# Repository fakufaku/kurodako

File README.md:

View this project on [CADLAB.io](https://cadlab.io/node/948). 

Kurodako
========

An eight-channel compact microphone array based on the Beaglebone Black and PDM microphones.

Bill of Materials
-----------------

* 8x SPM1437HM4H-B PDM MEMS Microphones (Mouser 721-SPM1437HM4H-B)
* 8x 100nF capacitors, 0805 package
* 2x pin headers 2x40, 2.54mm spaced

Possibly also:
* 4x 100 ohms resistors

If we want to use wires rather than only PCB microphones:
* 8x Micromatch Male-On-Wire 4 pin connector
* 8x Micromatch Female-One-Board 4 pin connector SMD
* flat cable, 1.27mm, 4 wires

Dependencies
------------

* The PRU code doing the low pass filtering [repo](https://github.com/Scrashdown/PRU-Audio-Processing) [Work in progress]

License
-------

2017 (c) Robin Scheibler

This board was designed by Robin Scheibler and is shared under the [Creative Commons CC-BY-SA](https://creativecommons.org/licenses/by-sa/4.0/) license.

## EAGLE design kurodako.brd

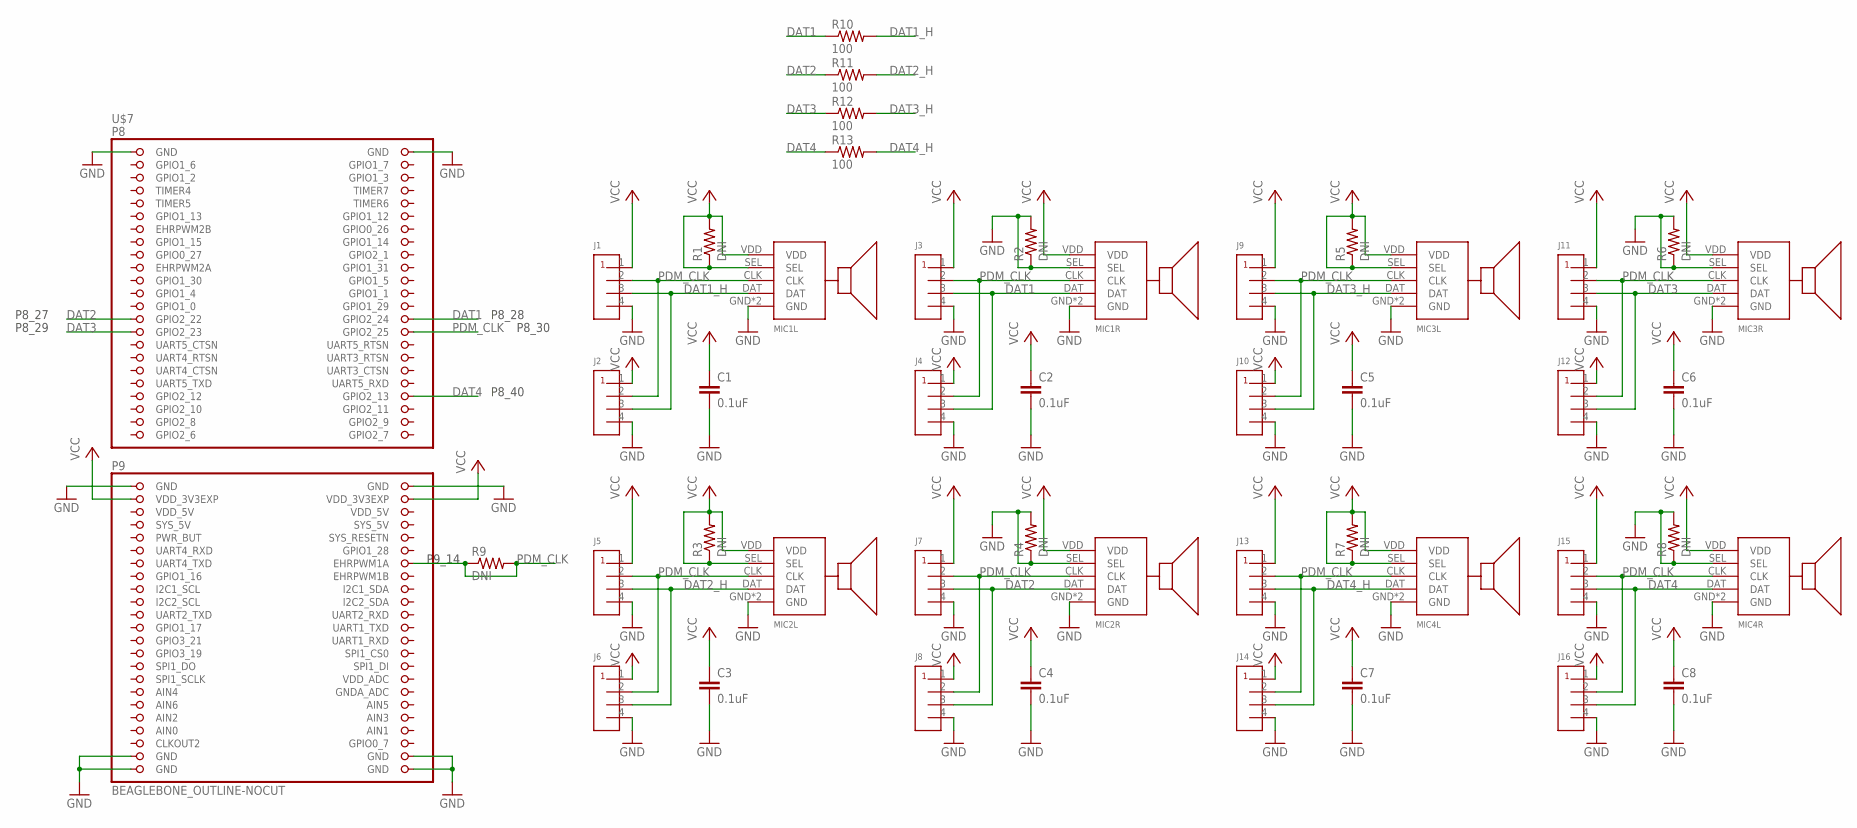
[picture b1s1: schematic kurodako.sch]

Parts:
C1, C2, C3, C4, C5, C6, C7, C8: 0.1uF; 0805
J1, J2, J3, J4, J5, J6, J7, J8, J9, J10, J11, J12, J13, J14, J15, J16: CONN-4P-MICROMATCH-SMD; MICROMATCH-4P-SMD
MIC1L, MIC1R, MIC2L, MIC2R, MIC3L, MIC3R, MIC4L, MIC4R: SPM1437HM4H-B; MEMS-MIC-6PAD
R1, R2, R3, R4, R5, R6, R7, R8, R9: DNI; R0805
R10, R11, R12, R13: 100; R0805
U$7: BEAGLEBONE_OUTLINE-NOCUT; BEAGLEBONE_SHIELD_NOCUT

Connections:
AIN0: U$7.85 (AIN0)
DAT1: J3.3, J4.3, MIC1R.DAT, R10.1, U$7.28 (GPIO2_24)
DAT1_H: J1.3, J2.3, MIC1L.DAT, R10.2
DAT2: J7.3, J8.3, MIC2R.DAT, R11.1, U$7.27 (GPIO2_22)
DAT2_H: J5.3, J6.3, MIC2L.DAT, R11.2
DAT3: J11.3, J12.3, MIC3R.DAT, R12.1, U$7.29 (GPIO2_23)
DAT3_H: J9.3, J10.3, MIC3L.DAT, R12.2
DAT4: J15.3, J16.3, MIC4R.DAT, R13.1, U$7.40 (GPIO2_13)
DAT4_H: J13.3, J14.3, MIC4L.DAT, R13.2
GND: C1.2, C2.2, C3.2, C4.2, C5.2, C6.2, C7.2, C8.2, J1.4, J2.4, J3.4, J4.4, J5.4, J6.4, J7.4, J8.4, J9.4, J10.4, J11.4, J12.4, J13.4, J14.4, J15.4, J16.4, MIC1L.GND, MIC1L.GND@1 (GND), MIC1R.GND, MIC1R.GND@1 (GND), MIC1R.SEL, MIC2L.GND, MIC2L.GND@1 (GND), MIC2R.GND, MIC2R.GND@1 (GND), MIC2R.SEL, MIC3L.GND, MIC3L.GND@1 (GND), MIC3R.GND, MIC3R.GND@1 (GND), MIC3R.SEL, MIC4L.GND, MIC4L.GND@1 (GND), MIC4R.GND, MIC4R.GND@1 (GND), MIC4R.SEL, R2.1, R2.2, R4.1, R4.2, R6.1, R6.2, R8.1, R8.2, U$7.1 (GND), U$7.2 (GND), U$7.47 (GND), U$7.48 (GND), U$7.89 (GND), U$7.90 (GND), U$7.91 (GND), U$7.92 (GND)
PDM_CLK: J1.2, J2.2, J3.2, J4.2, J5.2, J6.2, J7.2, J8.2, J9.2, J10.2, J11.2, J12.2, J13.2, J14.2, J15.2, J16.2, MIC1L.CLK, MIC1R.CLK, MIC2L.CLK, MIC2R.CLK, MIC3L.CLK, MIC3R.CLK, MIC4L.CLK, MIC4R.CLK, R9.1, R9.2, U$7.30 (GPIO2_25), U$7.60 (EHRPWM1A)
SYS_5V: U$7.53 (SYS_5V)
VCC: C1.1, C2.1, C3.1, C4.1, C5.1, C6.1, C7.1, C8.1, J1.1, J2.1, J3.1, J4.1, J5.1, J6.1, J7.1, J8.1, J9.1, J10.1, J11.1, J12.1, J13.1, J14.1, J15.1, J16.1, MIC1L.SEL, MIC1L.VDD, MIC1R.VDD, MIC2L.SEL, MIC2L.VDD, MIC2R.VDD, MIC3L.SEL, MIC3L.VDD, MIC3R.VDD, MIC4L.SEL, MIC4L.VDD, MIC4R.VDD, R1.1, R1.2, R3.1, R3.2, R5.1, R5.2, R7.1, R7.2, U$7.49 (VDD_3V3EXP), U$7.50 (VDD_3V3EXP)
VDD_5V: U$7.51 (VDD_5V), U$7.52 (VDD_5V)

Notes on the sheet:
P8_40
P8_27
P8_28
P8_29
P8_30
P9_14

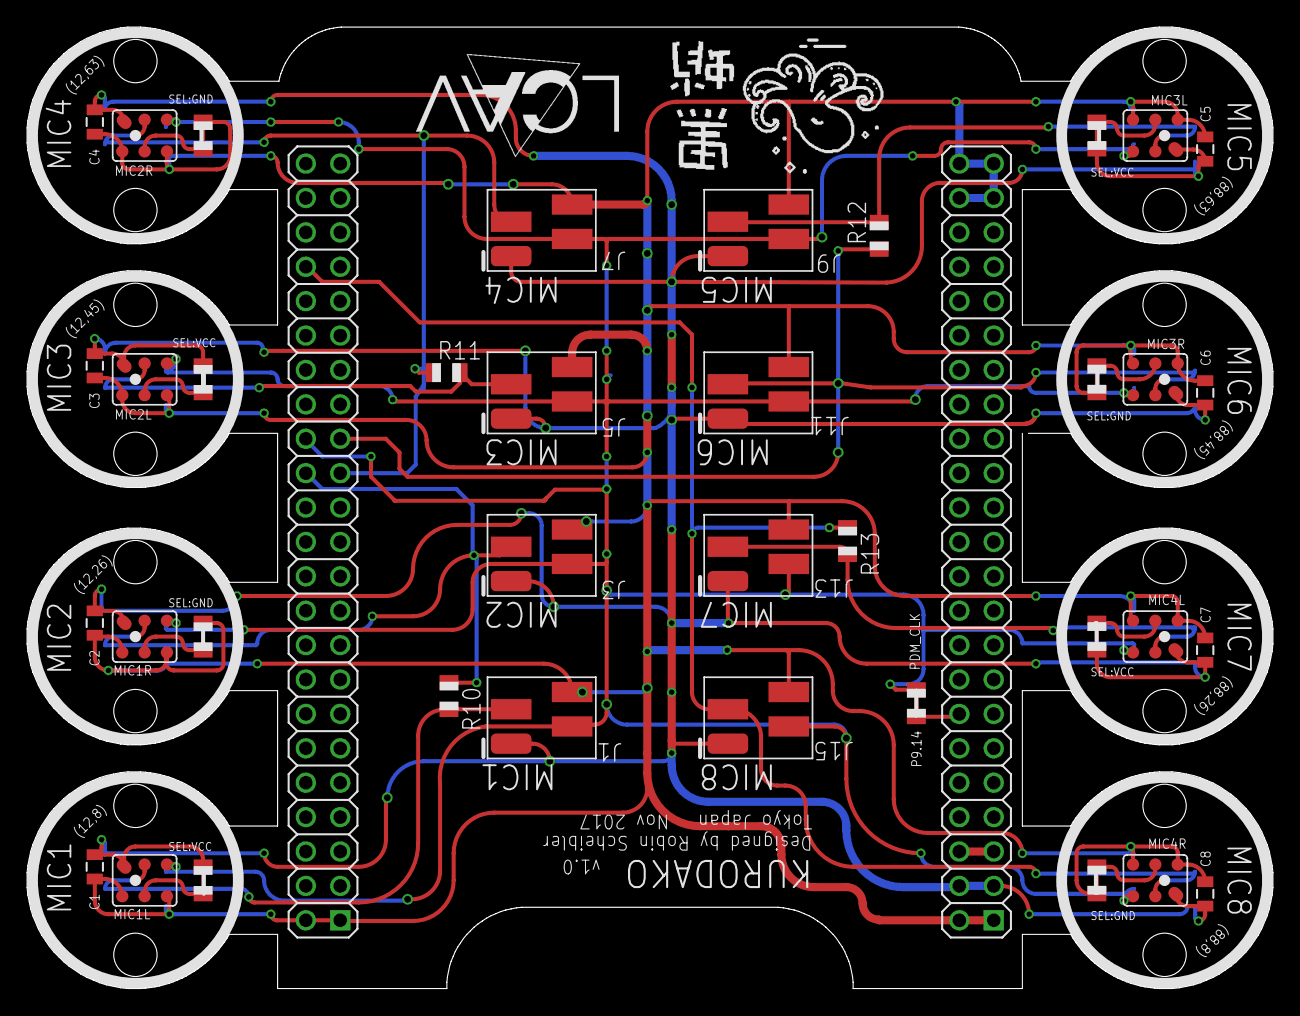
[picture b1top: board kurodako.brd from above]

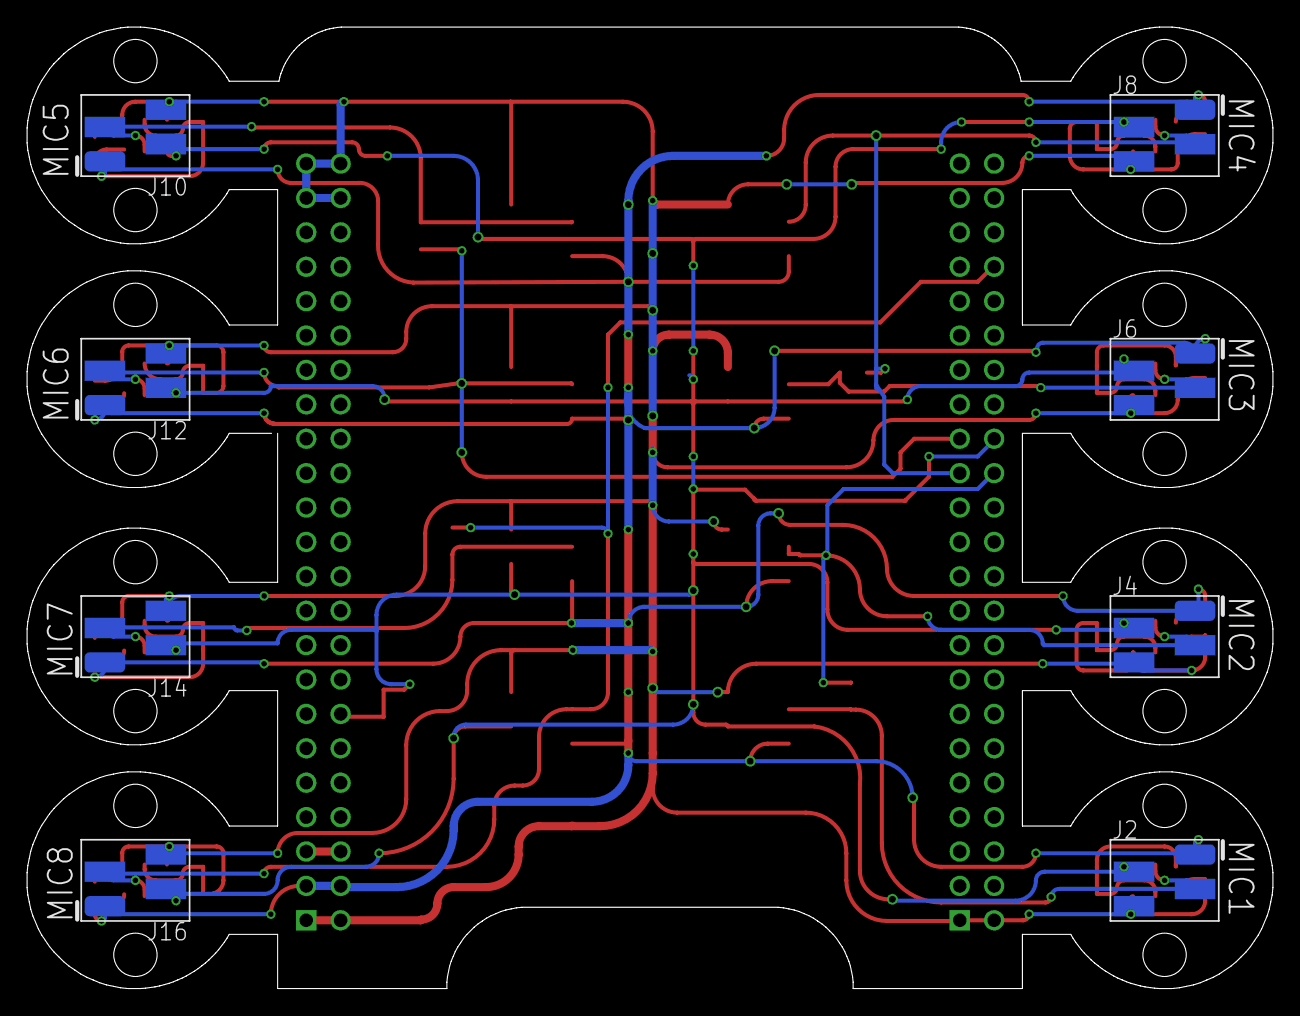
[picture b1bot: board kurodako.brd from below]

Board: 2 copper layers, 92.0 x 71.0 mm, 47 parts (8 on the bottom side), 12 nets.

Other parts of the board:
U$1: LCAV_LOGO_15MM

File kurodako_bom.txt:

Partlist exported from /Users/scheibler/Documents/eagle/Kurodako/kurodako.sch at 11.12.17 23:04

Part  Value                    Device                   Package                 Description                                        
C1    0.1uF                    CAP0805                  0805                    Capacitor                                          
C2    0.1uF                    CAP0805                  0805                    Capacitor                                          
C3    0.1uF                    CAP0805                  0805                    Capacitor                                          
C4    0.1uF                    CAP0805                  0805                    Capacitor                                          
C5    0.1uF                    CAP0805                  0805                    Capacitor                                          
C6    0.1uF                    CAP0805                  0805                    Capacitor                                          
C7    0.1uF                    CAP0805                  0805                    Capacitor                                          
C8    0.1uF                    CAP0805                  0805                    Capacitor                                          
J1    CONN-4P-MICROMATCH-SMD   CONN-4P-MICROMATCH-SMD   MICROMATCH-4P-SMD                                                          
J2    CONN-4P-MICROMATCH-SMD   CONN-4P-MICROMATCH-SMD   MICROMATCH-4P-SMD                                                          
J3    CONN-4P-MICROMATCH-SMD   CONN-4P-MICROMATCH-SMD   MICROMATCH-4P-SMD                                                          
J4    CONN-4P-MICROMATCH-SMD   CONN-4P-MICROMATCH-SMD   MICROMATCH-4P-SMD                                                          
J5    CONN-4P-MICROMATCH-SMD   CONN-4P-MICROMATCH-SMD   MICROMATCH-4P-SMD                                                          
J6    CONN-4P-MICROMATCH-SMD   CONN-4P-MICROMATCH-SMD   MICROMATCH-4P-SMD                                                          
J7    CONN-4P-MICROMATCH-SMD   CONN-4P-MICROMATCH-SMD   MICROMATCH-4P-SMD                                                          
J8    CONN-4P-MICROMATCH-SMD   CONN-4P-MICROMATCH-SMD   MICROMATCH-4P-SMD                                                          
J9    CONN-4P-MICROMATCH-SMD   CONN-4P-MICROMATCH-SMD   MICROMATCH-4P-SMD                                                          
J10   CONN-4P-MICROMATCH-SMD   CONN-4P-MICROMATCH-SMD   MICROMATCH-4P-SMD                                                          
J11   CONN-4P-MICROMATCH-SMD   CONN-4P-MICROMATCH-SMD   MICROMATCH-4P-SMD                                                          
J12   CONN-4P-MICROMATCH-SMD   CONN-4P-MICROMATCH-SMD   MICROMATCH-4P-SMD                                                          
J13   CONN-4P-MICROMATCH-SMD   CONN-4P-MICROMATCH-SMD   MICROMATCH-4P-SMD                                                          
J14   CONN-4P-MICROMATCH-SMD   CONN-4P-MICROMATCH-SMD   MICROMATCH-4P-SMD                                                          
J15   CONN-4P-MICROMATCH-SMD   CONN-4P-MICROMATCH-SMD   MICROMATCH-4P-SMD                                                          
J16   CONN-4P-MICROMATCH-SMD   CONN-4P-MICROMATCH-SMD   MICROMATCH-4P-SMD                                                          
MIC1L SPM1437HM4H-B            SPM1437HM4H-B            MEMS-MIC-6PAD                                                              
MIC1R SPM1437HM4H-B            SPM1437HM4H-B            MEMS-MIC-6PAD                                                              
MIC2L SPM1437HM4H-B            SPM1437HM4H-B            MEMS-MIC-6PAD                                                              
MIC2R SPM1437HM4H-B            SPM1437HM4H-B            MEMS-MIC-6PAD                                                              
MIC3L SPM1437HM4H-B            SPM1437HM4H-B            MEMS-MIC-6PAD                                                              
MIC3R SPM1437HM4H-B            SPM1437HM4H-B            MEMS-MIC-6PAD                                                              
MIC4L SPM1437HM4H-B            SPM1437HM4H-B            MEMS-MIC-6PAD                                                              
MIC4R SPM1437HM4H-B            SPM1437HM4H-B            MEMS-MIC-6PAD                                                              
R1    DNI                      R-US_R0805               R0805                   RESISTOR, American symbol                          
R2    DNI                      R-US_R0805               R0805                   RESISTOR, American symbol                          
R3    DNI                      R-US_R0805               R0805                   RESISTOR, American symbol                          
R4    DNI                      R-US_R0805               R0805                   RESISTOR, American symbol                          
R5    DNI                      R-US_R0805               R0805                   RESISTOR, American symbol                          
R6    DNI                      R-US_R0805               R0805                   RESISTOR, American symbol                          
R7    DNI                      R-US_R0805               R0805                   RESISTOR, American symbol                          
R8    DNI                      R-US_R0805               R0805                   RESISTOR, American symbol                          
R9    DNI                      R-US_R0805               R0805                   RESISTOR, American symbol                          
R10   100                      R-US_R0805               R0805                   RESISTOR, American symbol                          
R11   100                      R-US_R0805               R0805                   RESISTOR, American symbol                          
R12   100                      R-US_R0805               R0805                   RESISTOR, American symbol                          
R13   100                      R-US_R0805               R0805                   RESISTOR, American symbol                          
P8    2x23 pin header                                                           pin header 100 mil spacing
P9    2x23 pin header                                                           pin header 100 mil spacing

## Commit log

2017-11-28 Correct title in README.
2017-11-29 Added resistors on mic high and possiblity to change pdm clk.
2017-12-11 Added some values for the components on the schematics, a pdf of the schematics and the BOM.
2018-04-27 Backlink to CADLAB.io has been added.
